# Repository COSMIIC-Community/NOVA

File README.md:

# COSMIIC-NOVA
Open-source high channel count impantable devices

## NOVA BACKGROUND
NOVA or "Neural Open-source Versatile Array" is a sub-project of the Cleveland Open Source Modular Implant Innovators Community (COSMIIC). The project goal is to design high channel count implantable medical devices for neural recording and modulation that can be added as modules to the COSMIIC system. Within each device folder, you will find sub-folders that contain documentation of the enclosure and electronics design, testing, and regulatory communications. More information on the COSMIIC system can be found [here](https://cosmiic.org/).

## NOVA TEAM
Electronics design: Cynthia Chestek, Alex Vaskov, Dylan Wallace, Olivia Lee  
Mechanical design: Doug Shire, Janet Gbur, Sonny Behan  
Regulatory Sponsorship: Paul Cederna  
COSMIIC Integration: Kevin Kilgore, Brian Smith, Joris Lambrecht, Jeremiah Ukwela  

## LICENSING
All of our design files are open-source! You are free to reference, share, and adapt this material according to Creative Commons License Attribution 4.0 ([CC-By-4.0](https://creativecommons.org/licenses/by/4.0/)).
This license requires you to give appropriate credit and indiciate if changes were made. Attribution should be made to either Case Western Reserve University and/or University of Michigan. Attribution instructions are also found in each sub-folder. General instructions can be found [here](https://wiki.creativecommons.org/wiki/best_practices_for_attribution).

## FUNDING
This effort is funded by the National Institute of Health under the SPARC Human Open Research Neural Engineering Technologies (HORNET) Initiative. Award 1U41NS129436-01 sub-project 7004.
 
## DISCLAIMER
The contents of this repository are subject to revision. No representation or warranty, express or implied, is provided in relation to the accuracy, correctness, completeness, or reliability of the information, opinions, or conclusions expressed in this repository.

The contents of this repository (the “Materials”) are experimental in nature and should be used with prudence and appropriate caution. Any use is voluntary and at your own risk.

The Materials are made available “as is” by UM (the University of Michigan and its trustees, directors, officers, employees, faculty, students, agents, affiliated organizations and their insurance carriers, if any), and any other contributors to this repository (collectively, “Providers”). Providers expressly disclaim all warranties, express or implied, arising in connection with the Materials, or arising out of a course of performance, dealing, or trade usage, including, without limitation, any warranties of title, noninfringement, merchantability, or fitness for a particular purpose.

Any user of the Materials agrees to forever indemnify, defend, and hold harmless Providers from and against, and to waive any and all claims against Providers for any and all claims, suits, demands, liability, loss or damage whatsoever, including attorneys' fees, whether direct or consequential, on account of any loss, injury, death or damage to any person or (including without limitation all agents and employees of Providers and all property owned by, leased to or used by either Providers) or on account of any loss or damages to business or reputations or privacy of any persons, arising in whole or in part in any way from use of the Materials or in any way connected therewith or in any way related thereto.

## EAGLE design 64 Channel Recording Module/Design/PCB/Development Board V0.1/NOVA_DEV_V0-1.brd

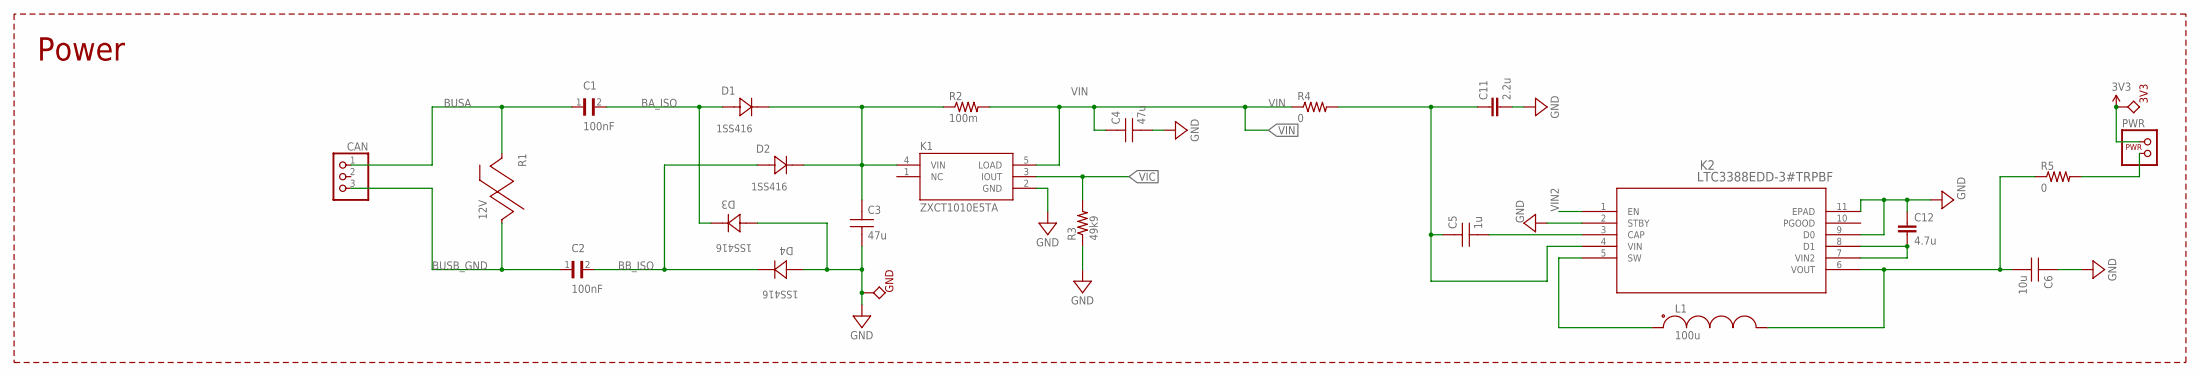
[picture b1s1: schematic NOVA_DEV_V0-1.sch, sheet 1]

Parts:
3V3: TPTP5001; TP5000OR5001
C1, C2: 100nF; CAPC1005X55N
C3, C4: 47u; C0603
C5: 1u; C0201
C6: 10u; C0603
C11: 2.2u; 0402
C12: 4.7u; 0402
CAN: PINHD-1X3; 1X03
D1, D2, D3, D4: 1SS416; SOD-923_TOS
GND: TPTP5001; TP5000OR5001
K1: ZXCT1010E5TA; SOT25
K2: LTC3388EDD-3#TRPBF; DFN-10_DD
L1: 100u; LPS4414
PWR: POWERJUMP; 1X04
R1: 12V; CG0603MLC
R2: 100m; R0201
R3: 49k9; 0201
R4, R5: 0; R0201

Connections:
3V3: 3V3.P$1, PWR.1, PWR.2 (1); also elsewhere on the board
BA_ISO: C1.2, D1.2 (ANODE), D3.1 (CATHODE)
BB_ISO: C2.2, D2.2 (ANODE), D4.1 (CATHODE)
BUSA: C1.1, CAN.1, R1.1; also elsewhere on the board
BUSB_GND: C2.1, CAN.3, R1.2; also elsewhere on the board
GND: C3.1, C4.1, C6.2, C11.2, C12.1, D3.2 (ANODE), D4.2 (ANODE), GND.P$1, K1.2 (GND), K2.2 (STBY), K2.9 (D0), K2.11 (EPAD), R3.1; also elsewhere on the board
unnamed: C5.2, C11.1, K2.4 (VIN), R4.2
unnamed: C12.2, K2.7 (VIN2), K2.8 (D1)
unnamed: C6.1, K2.6 (VOUT), L1.P$2, R5.1
unnamed: C5.1, K2.3 (CAP)
unnamed: C3.2, D1.1 (CATHODE), D2.1 (CATHODE), K1.4 (VIN), R2.1
unnamed: K2.5 (SW), L1.P$1
unnamed: PWR.3 (2), PWR.4 (2), R5.2
VIC: K1.3 (IOUT), R3.2; also elsewhere on the board
VIN: C4.2, K1.5 (LOAD), R2.2, R4.1; also elsewhere on the board
VIN2: K2.1 (EN); also elsewhere on the board

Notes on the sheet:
Power

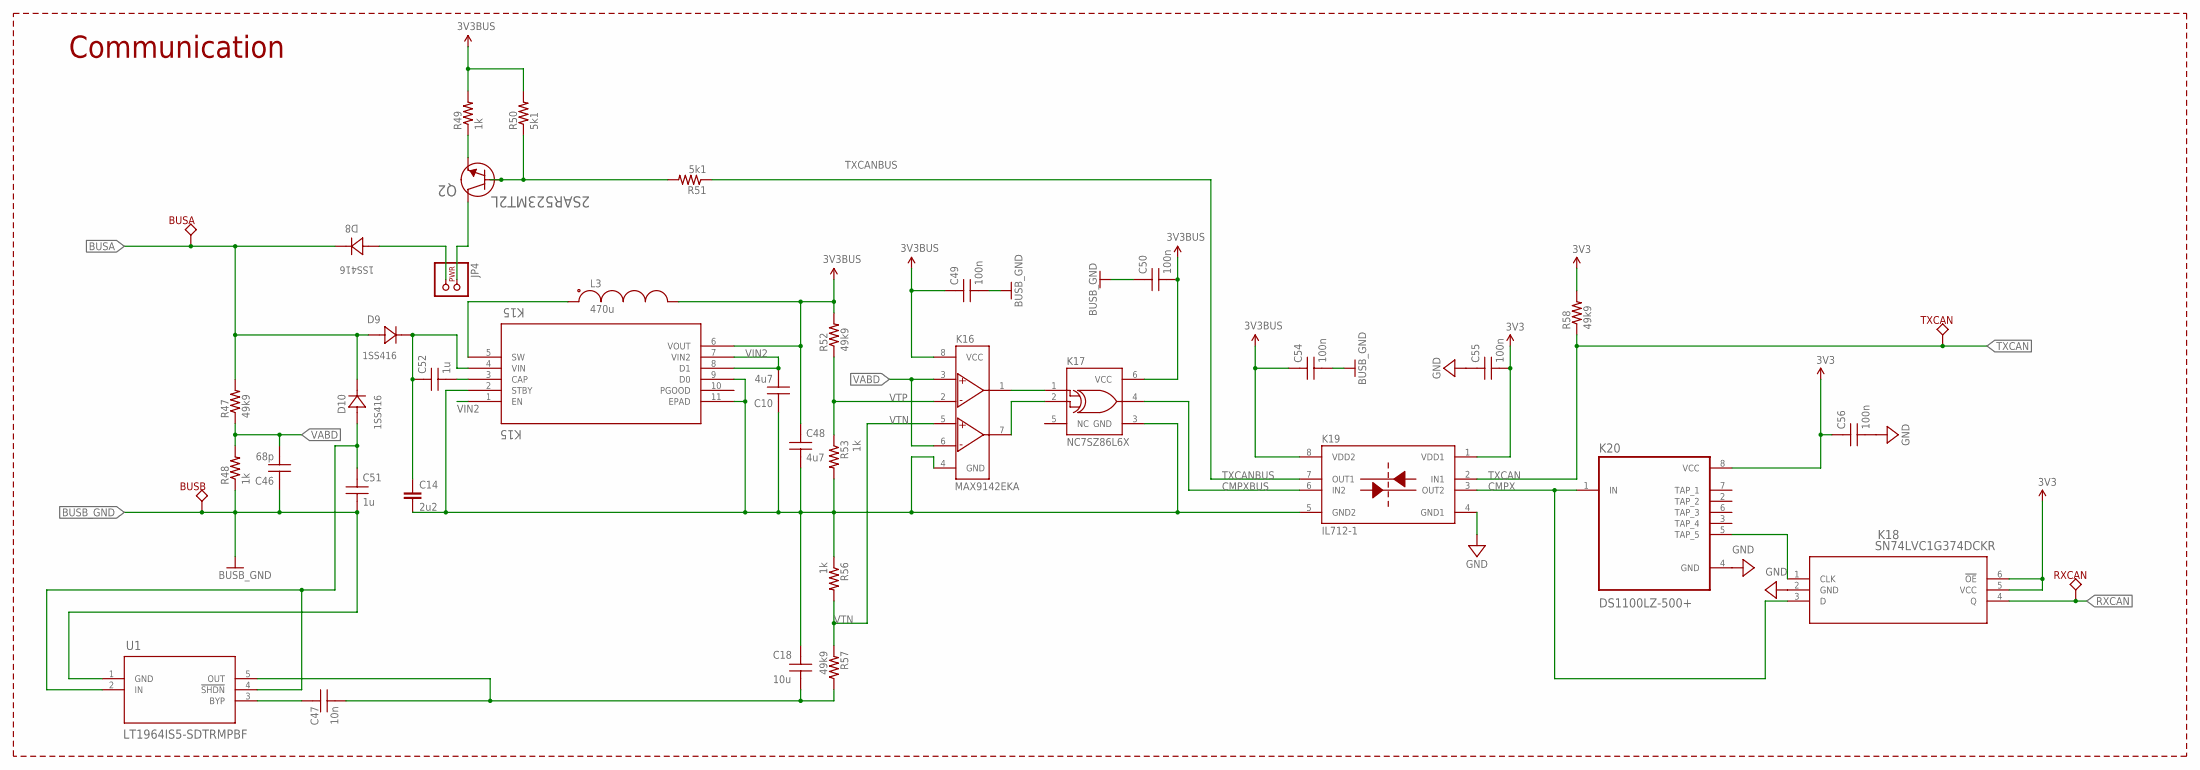
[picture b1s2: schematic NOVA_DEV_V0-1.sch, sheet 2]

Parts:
BUSA: TPTP5001; TP5000OR5001
BUSB: TPTP5001; TP5000OR5001
C10, C48: 4u7; C0402
C14: 2u2; 0402
C18: 10u; C0201
C46: 68p; C0201
C47: 10n; C0201
C49, C50, C54, C55, C56: 100n; C0201
C51, C52: 1u; C0201
D8, D9, D10: 1SS416; SOD-923_TOS
JP4: POWERJUMP; 1X04
K15: K15; DFN-10_DD
K16: MAX9142EKA; SOT23-8
K17: NC7SZ86L6X; MAC06A
K18: SN74LVC1G374DCKR; DCK6
K19: IL712-1; MSOP-8
K20: DS1100LZ-500+; SOIC127P600X175-8N
L3: 470u; CB2518
Q2: 2SAR523MT2L; TRANS_2SAR522M_ROM
R47, R52, R57, R58: 49k9; 0201
R48, R49, R53, R56: 1k; 0201
R50, R51: 5k1; 0201
RXCAN: TPTP5001; TP5000OR5001
TXCAN: TPTP5001; TP5000OR5001
U1: LT1964IS5-SDTRMPBF; TSOT23-5_S5_ADI

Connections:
3V3: C55.1, C56.2, K18.5 (VCC), K18.6 (!OE), K19.1 (VDD1), K20.8 (VCC), R58.2; also elsewhere on the board
3V3BUS: C48.2, C49.2, C50.1, C54.2, K15.6 (VOUT), K16.8 (VCC), K17.6 (VCC), K19.8 (VDD2), L3.2, R49.2, R50.2, R52.2
3V3BUS2: JP4.1, JP4.2 (1), Q2.1 (COLLECTOR)
BUSA: BUSA.P$1, D8.1 (CATHODE), D9.2 (ANODE), D10.1 (CATHODE), R47.2; also elsewhere on the board
BUSB_GND: BUSB.P$1, C46.2, C49.1, C50.2, C51.1, C54.1, R48.1, U1.1 (GND); also elsewhere on the board
CMPX: K18.3 (D), K19.3 (OUT2), K20.1 (IN)
CMPXBUS: K17.4 (Y), K19.6 (IN2)
GND: C55.2, C56.1, K18.2 (GND), K19.4 (GND1), K20.4 (GND); also elsewhere on the board
unnamed: K15.5 (SW), L3.1
unnamed: C10.2, C14.2, C18.2, C48.1, K15.2 (STBY), K15.9 (D0), K15.11 (EPAD), K16.4 (GND), K17.3 (GND), K19.5 (GND2), R53.2, R56.1
unnamed: C52.1, K15.3 (CAP)
unnamed: K18.1 (CLK), K20.5 (TAP_5)
unnamed: Q2.3 (EMITTER), R49.1
unnamed: C47.2, U1.3 (BYP)
unnamed: C14.1, C52.2, D9.1 (CATHODE), K15.4 (VIN)
unnamed: C51.2, D10.2 (ANODE), U1.2 (IN), U1.4 (!SHDN)
unnamed: C18.1, C47.1, R57.1, U1.5 (OUT)
unnamed: Q2.2 (BASE), R50.1, R51.2
unnamed: K16.1 (OUT1), K17.1 (A)
unnamed: K16.7 (OUT2), K17.2 (B)
unnamed: D8.2 (ANODE), JP4.3 (2), JP4.4 (2)
RXCAN: K18.4 (Q), RXCAN.P$1; also elsewhere on the board
TXCAN: K19.2 (IN1), R58.1, TXCAN.P$1; also elsewhere on the board
TXCANBUS: K19.7 (OUT1), R51.1
VABD: C46.1, K16.3 (+IN1), K16.6 (-IN2), R47.1, R48.2
VIN2: C10.1, K15.1 (EN), K15.7 (VIN2), K15.8 (D1); also elsewhere on the board
VTN: K16.5 (+IN2), R56.2, R57.2
VTP: K16.2 (-IN1), R52.1, R53.1

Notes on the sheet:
Communication

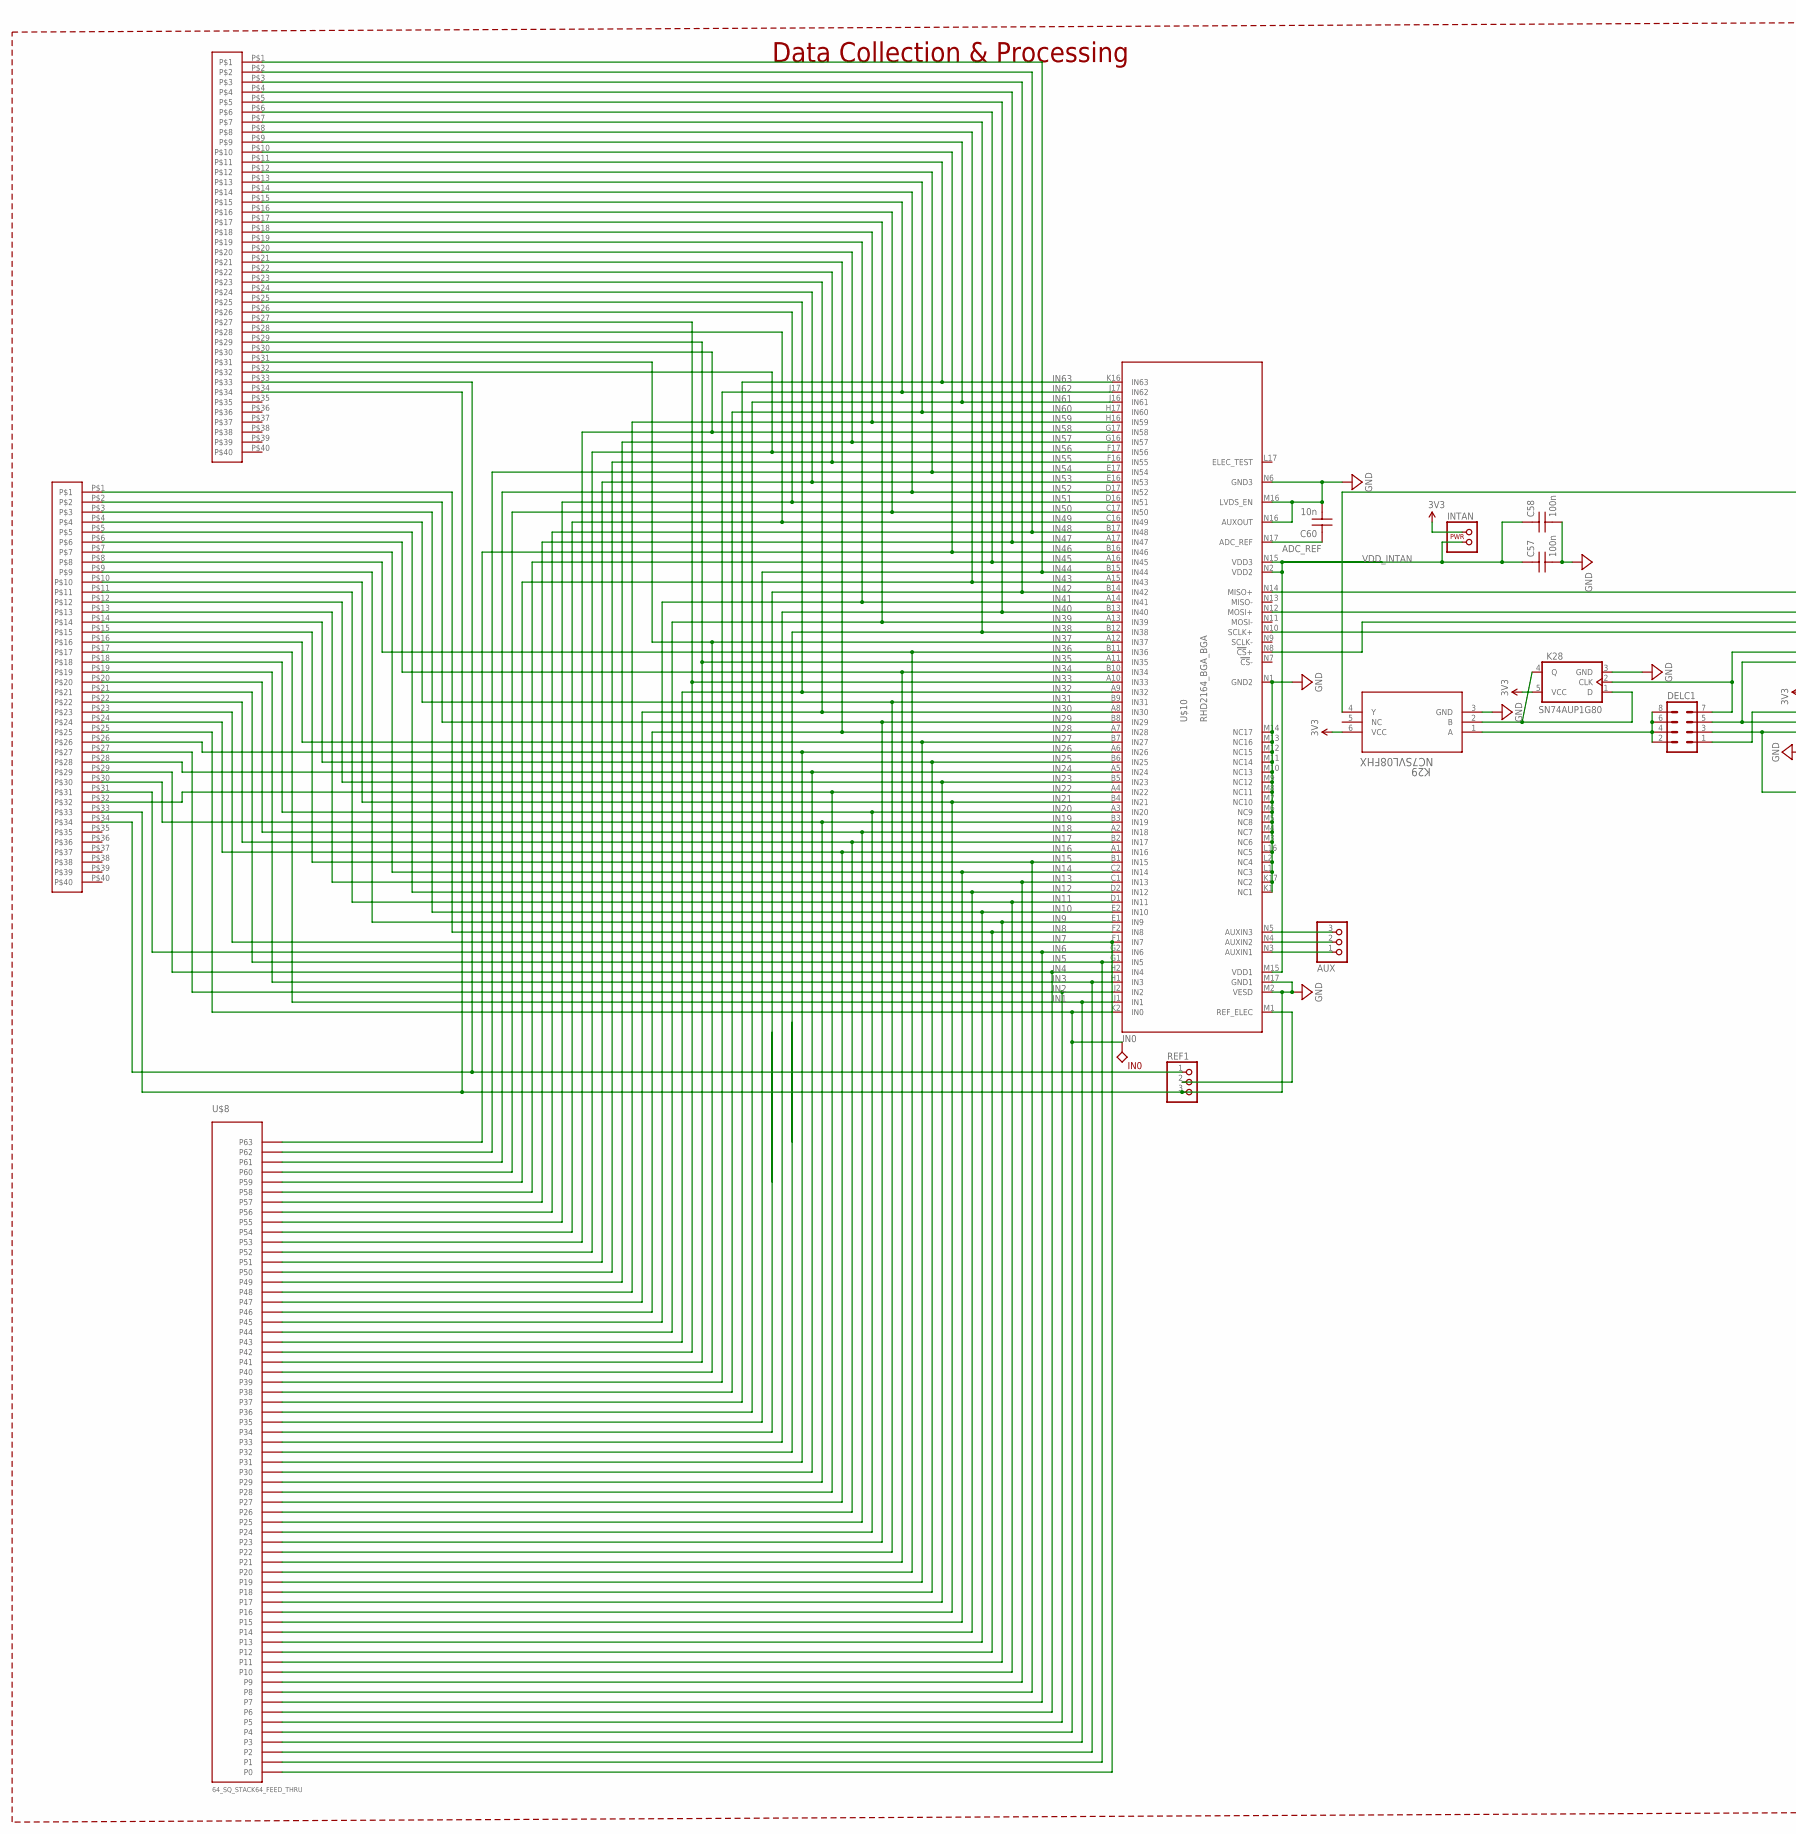
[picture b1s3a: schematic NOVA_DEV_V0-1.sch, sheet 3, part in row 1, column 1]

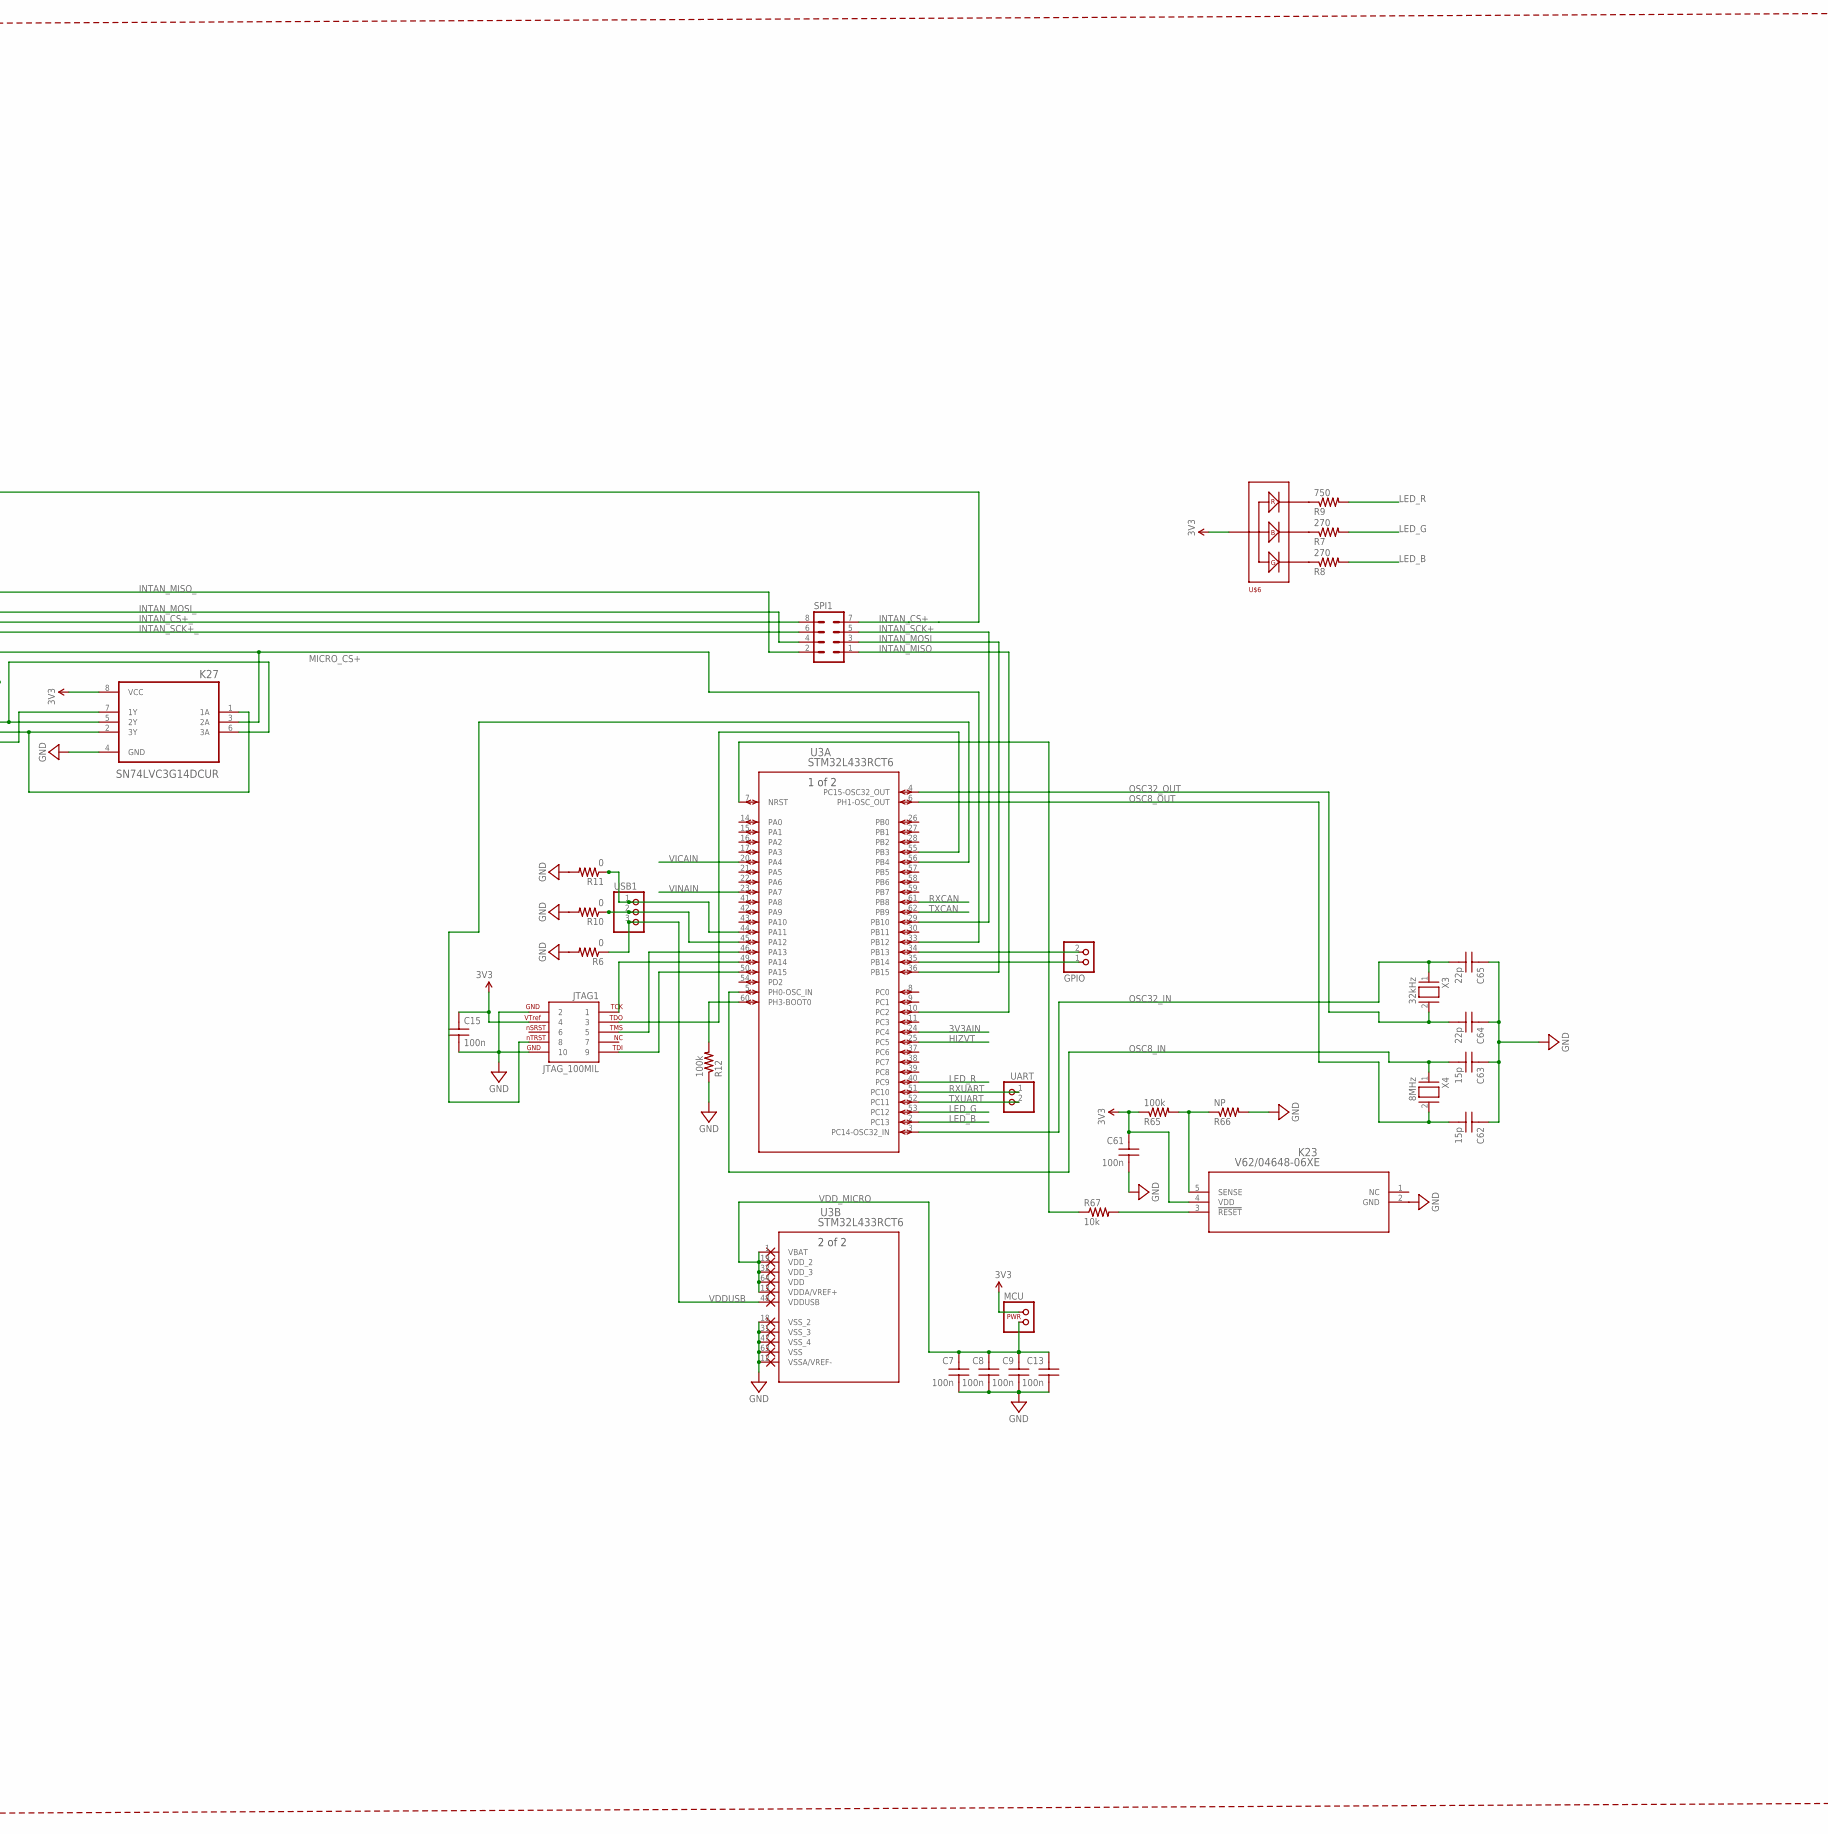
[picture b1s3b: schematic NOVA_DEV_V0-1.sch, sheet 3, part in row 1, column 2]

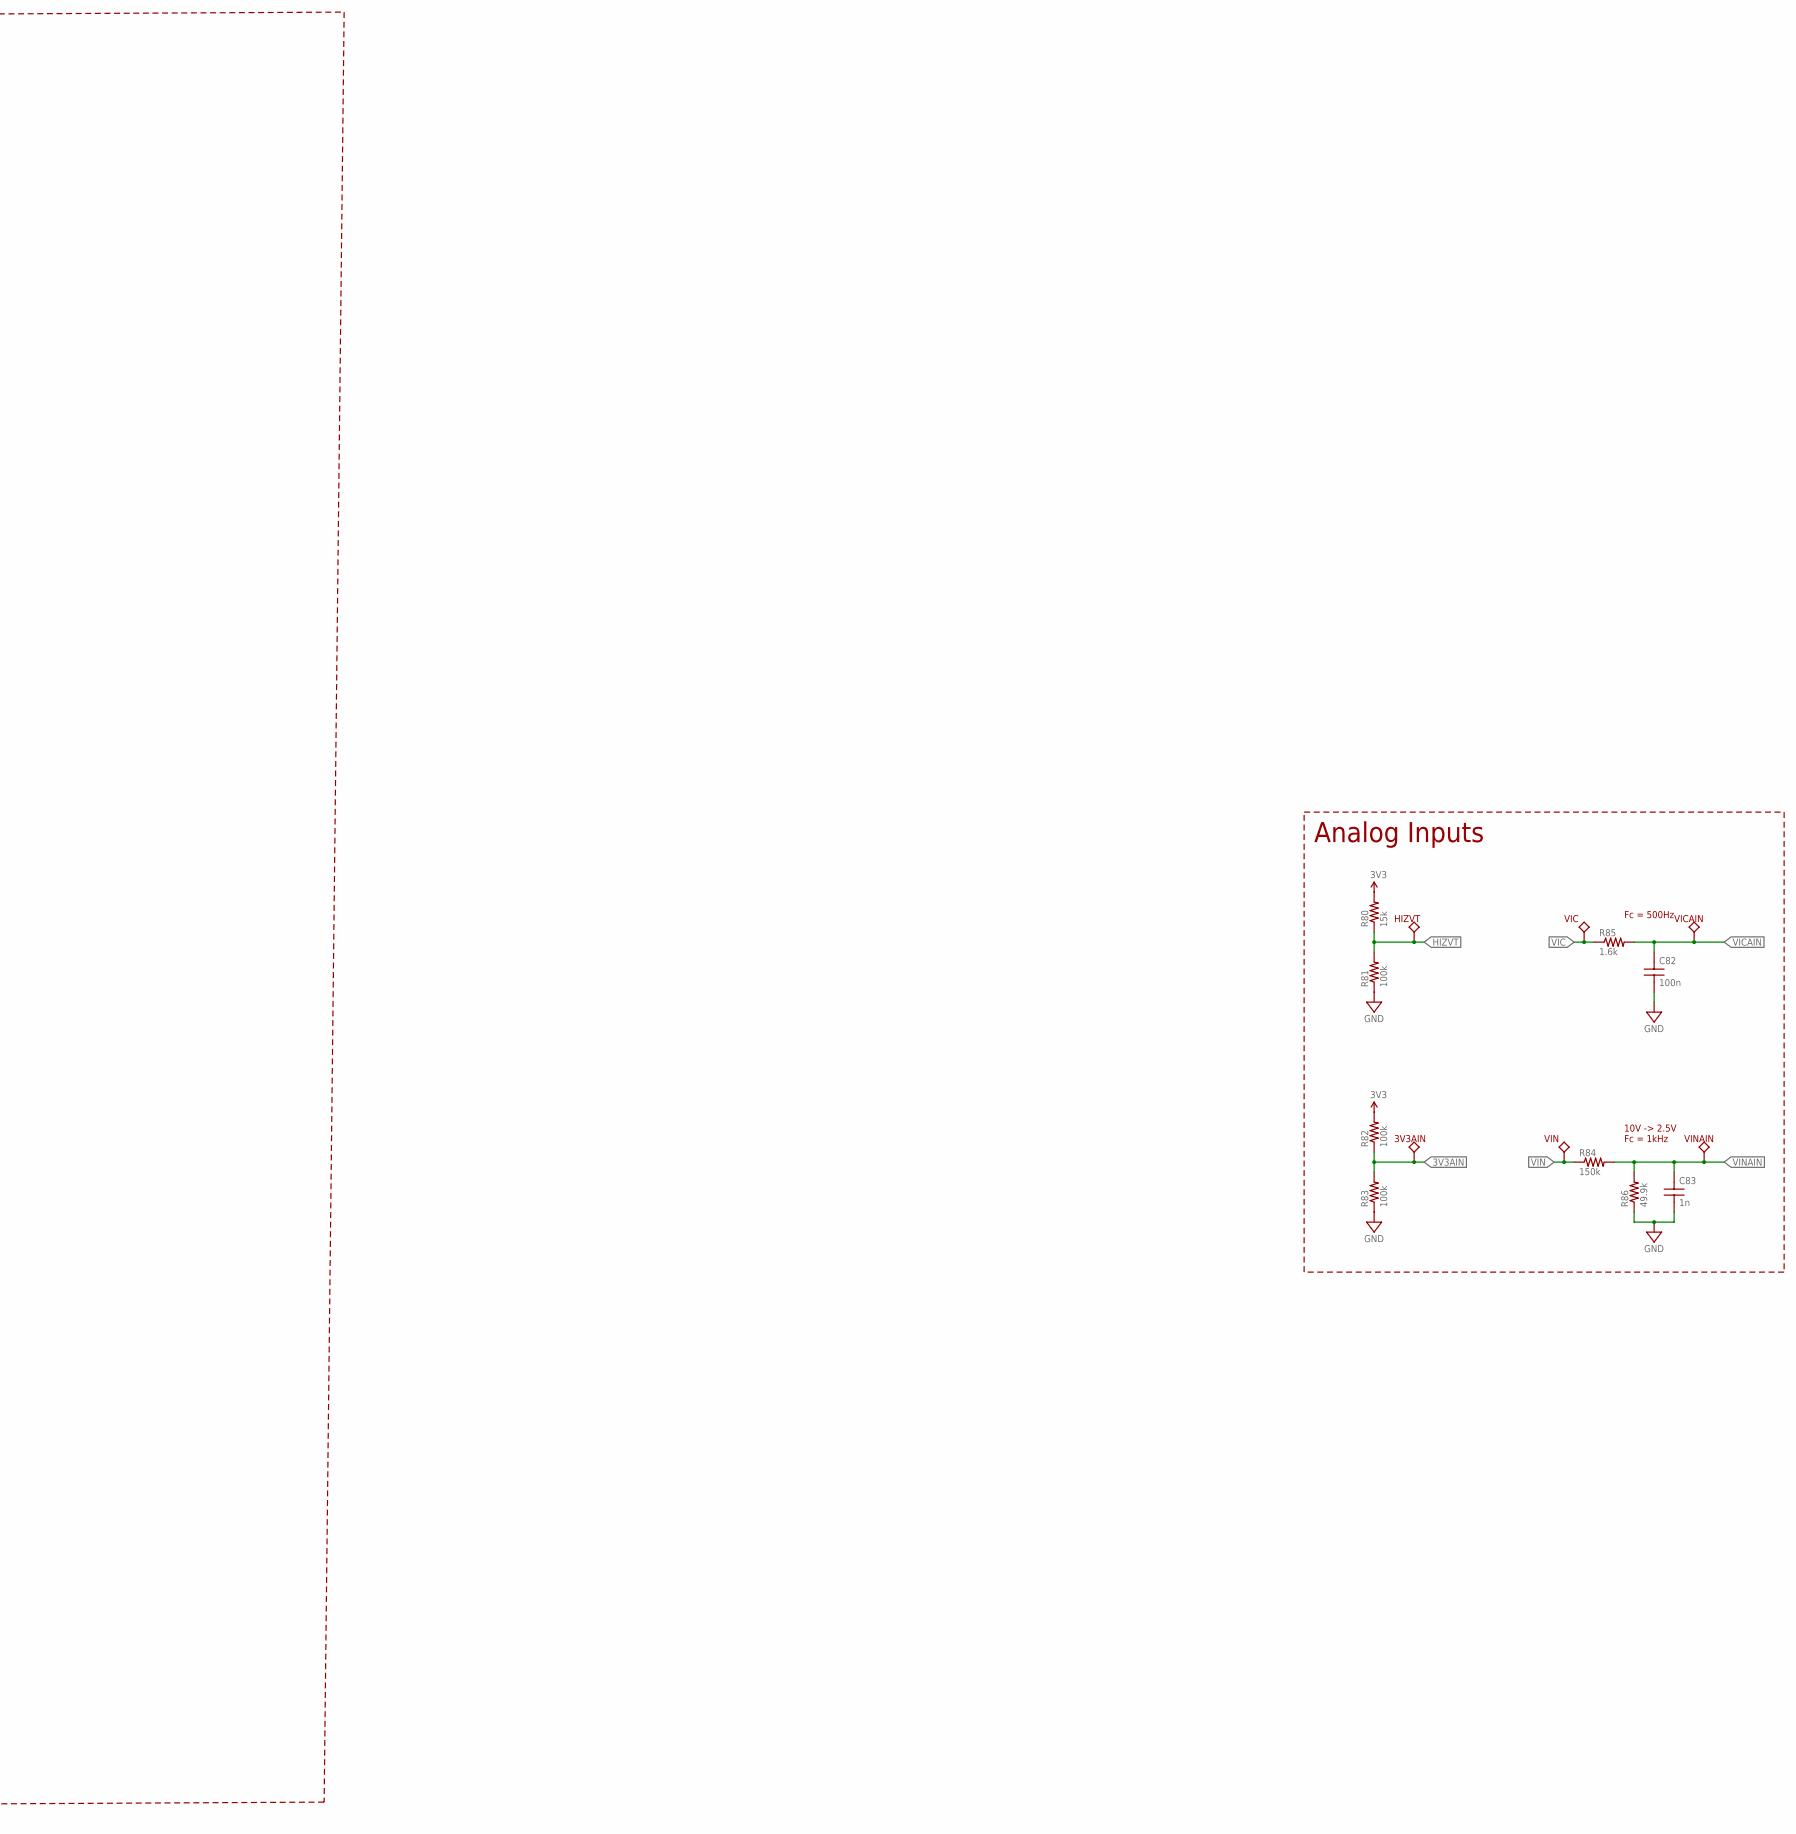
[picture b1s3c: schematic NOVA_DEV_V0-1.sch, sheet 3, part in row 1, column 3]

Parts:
3V3AIN: TPTP5001; TP5000OR5001
AUX: PINHD-1X3; 1X03
C7, C8, C9, C13, C15, C57, C58, C61, C82: 100n; C0201
C60: 10n; C0201
C62, C63: 15p; C0402
C64, C65: 22p; C0402
C83: 1n; C0201
DELC1: MA04-2
GPIO: PINHD-1X2; 1X02
HIZVT: TPTP5001; TP5000OR5001
IN0: TPTP5001; TP5000OR5001
INTAN: POWERJUMP; 1X04
JTAG1: JTAG_100MIL; JTAG-10
K23: V62/04648-06XE; DCK5
K27: SN74LVC3G14DCUR; SOP50P310X90-8N
K28: SN74AUP1G80; SOT23-5
K29: NC7SVL08FHX; MICROPAK2-6_1X1_ONS
MCU: POWERJUMP; 1X04
R6, R10, R11: 0; R0201
R7, R8: 270; R0201
R9: 750; R0201
R12, R65, R81, R82, R83: 100k; R0201
R66: NP; R0201
R67: 10k; R0201
R80: 15k; R0201
R84: 150k; R0201
R85: 1.6k; R0201
R86: 49.9k; 0201
REF1: PINHD-1X3; 1X03
SPI1: MA04-2
U3: STM32L433RCT6; LQFP64-10X10MM
U$3, U$4: 40-PIN-SAMTEC; SAMTECSFH120-01-X-D-SM-LC
U$6: WINI_KINGBRIGHT_APHF1608LSEEQBDZGKC; WINI_4-SMD
U$8: 64_SQ_STACK64_FEED_THRU; 64_FEED_THRU
U$10: RHD2164_BGA_BGA; BGA104_9X7
UART: PINHD-1X2; 1X02
USB1: PINHD-1X3; 1X03
VIC: TPTP5001; TP5000OR5001
VICAIN: TPTP5001; TP5000OR5001
VIN: TPTP5001; TP5000OR5001
VINAIN: TPTP5001; TP5000OR5001
X3: 32kHz; ABS07
X4: 8MHz; NX5032GA

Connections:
3V3: C15.2, C61.2, INTAN.1, INTAN.2 (1), JTAG1.4, K23.4 (VDD), K27.8 (VCC), K28.5 (VCC), K29.6 (VCC), MCU.1, MCU.2 (1), R65.1, R80.2, R82.2, U$6.V+; also elsewhere on the board
3V3AIN: 3V3AIN.P$1, R82.1, R83.2, U3.24 (PC4)
ADC_REF: C60.2, U$10.N17 (ADC_REF)
GND: C7.1, C8.1, C9.1, C13.1, C15.1, C57.1, C58.1, C60.1, C61.1, C62.2, C63.2, C64.2, C65.2, C82.1, C83.1, JTAG1.2, JTAG1.10, K23.2 (GND), K27.4 (GND), K28.3 (GND), K29.3 (GND), R6.2, R10.2, R11.2, R12.1, R66.2, R81.1, R83.1, R86.1, REF1.3, U3.12 (VSSA/VREF-), U3.18 (VSS_2), U3.31 (VSS_3), U3.47 (VSS_4), U3.63 (VSS), U$3.P$34, U$4.P$33, U$10.K1 (NC1), U$10.K17 (NC2), U$10.L1 (NC3), U$10.L2 (NC4), U$10.L16 (NC5), U$10.M2 (VESD), U$10.M3 (NC6), U$10.M4 (NC7), U$10.M5 (NC8), U$10.M6 (NC9), U$10.M7 (NC10), U$10.M8 (NC11), U$10.M9 (NC12), U$10.M10 (NC13), U$10.M11 (NC14), U$10.M12 (NC15), U$10.M13 (NC16), U$10.M14 (NC17), U$10.M16 (LVDS_EN), U$10.M17 (GND1), U$10.N1 (GND2), U$10.N6 (GND3), U$10.N16 (AUXOUT); also elsewhere on the board
HIZVT: HIZVT.P$1, R80.1, R81.2, U3.25 (PC5)
IN0: IN0.P$1, U$4.P$25, U$8.P$5 (P4), U$10.K2 (IN0)
IN1: U$4.P$17, U$8.P$4 (P3), U$10.J1 (IN1)
IN2: U$4.P$27, U$8.P$6 (P5), U$10.J2 (IN2)
IN3: U$4.P$19, U$8.P$3 (P2), U$10.H1 (IN3)
IN4: U$4.P$29, U$8.P$7 (P6), U$10.H2 (IN4)
IN5: U$4.P$21, U$8.P$2 (P1), U$10.G1 (IN5)
IN6: U$4.P$31, U$8.P$8 (P7), U$10.G2 (IN6)
IN7: U$4.P$23, U$8.P$1 (P0), U$10.F1 (IN7)
IN8: U$4.P$1, U$8.P$13 (P12), U$10.F2 (IN8)
IN9: U$4.P$9, U$8.P$12 (P11), U$10.E1 (IN9)
IN10: U$4.P$3, U$8.P$14 (P13), U$10.E2 (IN10)
IN11: U$4.P$11, U$8.P$11 (P10), U$10.D1 (IN11)
IN12: U$4.P$5, U$8.P$15 (P14), U$10.D2 (IN12)
IN13: U$4.P$13, U$8.P$10 (P9), U$10.C1 (IN13)
IN14: U$4.P$7, U$8.P$16 (P15), U$10.C2 (IN14)
IN15: U$4.P$15, U$8.P$9 (P8), U$10.B1 (IN15)
IN16: U$4.P$24, U$8.P$28 (P27), U$10.A1 (IN16)
IN17: U$4.P$22, U$8.P$27 (P26), U$10.B2 (IN17)
IN18: U$4.P$20, U$8.P$26 (P25), U$10.A2 (IN18)
IN19: U$4.P$30, U$8.P$30 (P29), U$10.B3 (IN19)
IN20: U$4.P$18, U$8.P$25 (P24), U$10.A3 (IN20)
IN21: U$4.P$10, U$8.P$17 (P16), U$10.B4 (IN21)
IN22: U$4.P$32, U$8.P$29 (P28), U$10.A4 (IN22)
IN23: U$4.P$12, U$8.P$18 (P17), U$10.B5 (IN23)
IN24: U$4.P$28, U$8.P$31 (P30), U$10.A5 (IN24)
IN25: U$4.P$14, U$8.P$19 (P18), U$10.B6 (IN25)
IN26: U$4.P$26, U$8.P$32 (P31), U$10.A6 (IN26)
IN27: U$4.P$16, U$8.P$20 (P19), U$10.B7 (IN27)
IN28: U$3.P$21, U$8.P$47 (P46), U$10.A7 (IN28)
IN29: U$4.P$2, U$8.P$24 (P23), U$10.B8 (IN29)
IN30: U$3.P$23, U$8.P$48 (P47), U$10.A8 (IN30)
IN31: U$4.P$4, U$8.P$23 (P22), U$10.B9 (IN31)
IN32: U$3.P$25, U$8.P$44 (P43), U$10.A9 (IN32)
IN33: U$3.P$27, U$8.P$43 (P42), U$10.A10 (IN33)
IN34: U$4.P$6, U$8.P$22 (P21), U$10.B10 (IN34)
IN35: U$3.P$29, U$8.P$42 (P41), U$10.A11 (IN35)
IN36: U$4.P$8, U$8.P$21 (P20), U$10.B11 (IN36)
IN37: U$3.P$31, U$8.P$41 (P40), U$10.A12 (IN37)
IN38: U$3.P$7, U$8.P$33 (P32), U$10.B12 (IN38)
IN39: U$3.P$17, U$8.P$45 (P44), U$10.A13 (IN39)
IN40: U$3.P$5, U$8.P$34 (P33), U$10.B13 (IN40)
IN41: U$3.P$19, U$8.P$46 (P45), U$10.A14 (IN41)
IN42: U$3.P$3, U$8.P$35 (P34), U$10.B14 (IN42)
IN43: U$3.P$8, U$8.P$60 (P59), U$10.A15 (IN43)
IN44: U$3.P$1, U$8.P$36 (P35), U$10.B15 (IN44)
IN45: U$3.P$6, U$8.P$59 (P58), U$10.A16 (IN45)
IN46: U$3.P$10, U$8.P$64 (P63), U$10.B16 (IN46)
IN47: U$3.P$4, U$8.P$58 (P57), U$10.A17 (IN47)
IN48: U$3.P$2, U$8.P$57 (P56), U$10.B17 (IN48)
IN49: U$3.P$28, U$8.P$55 (P54), U$10.C16 (IN49)
IN50: U$3.P$16, U$8.P$61 (P60), U$10.C17 (IN50)
IN51: U$3.P$26, U$8.P$56 (P55), U$10.D16 (IN51)
IN52: U$3.P$14, U$8.P$62 (P61), U$10.D17 (IN52)
IN53: U$3.P$24, U$8.P$52 (P51), U$10.E16 (IN53)
IN54: U$3.P$12, U$8.P$63 (P62), U$10.E17 (IN54)
IN55: U$3.P$22, U$8.P$51 (P50), U$10.F16 (IN55)
IN56: U$3.P$32, U$8.P$53 (P52), U$10.F17 (IN56)
IN57: U$3.P$20, U$8.P$50 (P49), U$10.G16 (IN57)
IN58: U$3.P$30, U$8.P$54 (P53), U$10.G17 (IN58)
IN59: U$3.P$18, U$8.P$49 (P48), U$10.H16 (IN59)
IN60: U$3.P$13, U$8.P$39 (P38), U$10.H17 (IN60)
IN61: U$3.P$9, U$8.P$37 (P36), U$10.J16 (IN61)
IN62: U$3.P$15, U$8.P$40 (P39), U$10.J17 (IN62)
IN63: U$3.P$11, U$8.P$38 (P37), U$10.K16 (IN63)
INTAN_CS+: K29.4 (Y), SPI1.7
INTAN_CS+_: SPI1.8, U$10.N8 (!CS!+)
INTAN_MISO: SPI1.1, U3.10 (PC2)
INTAN_MISO_: SPI1.2, U$10.N14 (MISO+)
INTAN_MOSI: SPI1.3, U3.36 (PB15)
INTAN_MOSI_: SPI1.4, U$10.N12 (MOSI+)
INTAN_SCK+: SPI1.5, U3.29 (PB10)
INTAN_SCK+_: SPI1.6, U$10.N10 (SCLK+)
LED_B: R8.2, U3.2 (PC13)
LED_G: R7.2, U3.53 (PC12)
LED_R: R9.2, U3.40 (PC9)
MICRO_CS+: DELC1.7, K27.3 (2A), K28.2 (CLK), U3.33 (PB12)
unnamed: R67.1, U3.7 (NRST)
unnamed: AUX.1, U$10.N3 (AUXIN1)
unnamed: R12.2, U3.60 (PH3-BOOT0)
unnamed: AUX.2, U$10.N4 (AUXIN2)
unnamed: GPIO.2, U3.34 (PB13)
unnamed: DELC1.2, DELC1.4, DELC1.6, DELC1.8, K29.1 (A)
unnamed: DELC1.5, K27.5 (2Y), K27.6 (3A)
unnamed: GPIO.1, U3.35 (PB14)
unnamed: DELC1.3, K27.1 (1A), K27.2 (3Y)
unnamed: DELC1.1, K27.7 (1Y)
unnamed: AUX.3, U$10.N5 (AUXIN3)
unnamed: K23.3 (!RESET), R67.2
unnamed: REF1.1, U$3.P$33, U$4.P$34
unnamed: JTAG1.8, U3.56 (PB4)
unnamed: JTAG1.5, U3.46 (PA13)
unnamed: REF1.2, U$10.M1 (REF_ELEC)
unnamed: R7.1, U$6.B
unnamed: JTAG1.1, U3.49 (PA14)
unnamed: JTAG1.9, U3.50 (PA15)
unnamed: JTAG1.3, U3.55 (PB3)
unnamed: R8.1, U$6.G
unnamed: R9.1, U$6.R
unnamed: R11.1, U3.44 (PA11), USB1.1
unnamed: R10.1, U3.45 (PA12), USB1.2
unnamed: K23.5 (SENSE), R65.2, R66.1
unnamed: K28.1 (D), K28.4 (Q), K29.2 (B)
OSC8_IN: C63.1, U3.5 (PH0-OSC_IN), X4.1
OSC8_OUT: C62.1, U3.6 (PH1-OSC_OUT), X4.2
OSC32_IN: C65.1, U3.3 (PC14-OSC32_IN), X3.1
OSC32_OUT: C64.1, U3.4 (PC15-OSC32_OUT), X3.2
RXCAN: U3.61 (PB8); also elsewhere on the board
RXUART: U3.51 (PC10), UART.1
TXCAN: U3.62 (PB9); also elsewhere on the board
TXUART: U3.52 (PC11), UART.2
VDDUSB: R6.1, U3.48 (VDDUSB), USB1.3
VDD_INTAN: C57.2, C58.2, INTAN.3 (2), INTAN.4 (2), U$10.M15 (VDD1), U$10.N2 (VDD2), U$10.N15 (VDD3)
VDD_MICRO: C7.2, C8.2, C9.2, C13.2, MCU.3 (2), MCU.4 (2), U3.1 (VBAT), U3.13 (VDDA/VREF+), U3.19 (VDD_2), U3.32 (VDD_3), U3.64 (VDD)
VIC: R85.1, VIC.P$1; also elsewhere on the board
VICAIN: C82.2, R85.2, U3.20 (PA4), VICAIN.P$1
VIN: R84.1, VIN.P$1; also elsewhere on the board
VINAIN: C83.2, R84.2, R86.2, U3.23 (PA7), VINAIN.P$1

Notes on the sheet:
Data Collection & Processing
Analog Inputs
Fc = 500Hz
10V -> 2.5V Fc = 1kHz

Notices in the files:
parts and their libraries:
COPYRIGHT: Copyright (C) 2022 Ultra Librarian. All rights reserved.
COPYRIGHT: Copyright (C) 2023 Ultra Librarian. All rights reserved.
